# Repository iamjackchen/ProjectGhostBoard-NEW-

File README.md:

# ProjectGhostBoard

Hello thereeee

This is a site for me to document my current ongoing project a low profile wireless mechanical keyboard. Originally started this a few years ago back when I was in middle school (my macbook air had a semi-broken keyboard and I was just getting into the world of mechanical keyboards, AND there was a new set of low profile mechanical switches on the market) 

But who even knows anything about electronics engineering at that age? Took me a few years and attempts to slowly figure stuff out (you can see where I got to in my last attempt here, made when I was in G10: https://github.com/iamjackchen/ProjectGhostboard-OLD-)

<br/>

### About the Project

Enough with the history, moving onto the project itself. The original design goal was to build a low profile (i.e. portable) mechanical keyboard. The portable aspect also prompted me to pursue Bluetooth functionality ~~which might have possibly been the worst decision I have ever made in terms of trying to actually finish this project~~.
Here were my original design blueprints: 

<br/>

<br/>

The design has evolved a little (along with my knowledge of embedded systems and keyboard assembly 😂) but the general principle remains the same. A 75%-ish layout with PCB-mounted low profile switches (PG1350 - I'm using the brown/tactile variant) and white multi-level backlight. No disgusting rgb. Originally when the PG1350 line was released I tried to make this the first true low-profile wireless keyboard on the market but obviously that didn't happen lmao. The layout I eventually settled for is below:

<br/>

<br/>

The current PCB design (in the electronics folder) uses a USB-power gated MOSFET to regulate power delivery from the battery to the main circuit, an MCU-gated MOSFET to control charging (power flow to the battery) and a MCU-gated MOSFET to trigger Bluetooth. The intention of the MCU-gated control charging MOSFET is for the user to be able to disable charging when the keyboard is being plugged in over long periods of time for battery longevity. I'll probably use raw-hid to have some sort of computer-keyboard communication and write a desktop client that can tell the keyboard to disable charging. Maybe in the futre I can use raw-hid and a desktop client for other purposes (macros, backlight settings, and etc)

Some other design considerations and features with regards to electronics:
  - USB Type C
  - Battery charge indicator
  - HID over BLE

The software that makes all of this come together is [QMK](https://github.com/qmk/qmk_firmware). It's a keyboard firmware written in C and I am immensely grateful to its creators. And yes, for all new programmers here, do learn C or C++ before Python and *not* the other way around. You will thank me.

I havent gotten far enough to worry too much about the physical enclosure and keyboard assembly but I will have (hopefully) some CAD files, screenshots, and renders hanging out in this repo soon!! As of now I am aware that the PG1350 requires a thinner (1.2mm) plate and the stabilisers are mounted to the PCB (with plate cutouts needed). 

<br/>
If you've read this far, thank you so much for taking interest, and I hope to bear good news of progress soon. Below is a gallery of certain snippets from this awesome journey. 

----

# Gallery

### Current PCB Progress Renders (Coming soon)
Stay tuned.

<br/>

### Power Delivery Circuit Tester
Small PCB to test out my USB-C power delivery designs. Used an IC originally meant for power bank charging (IP5306 if anyone's interested) along with an FS8205A and a DW01 for battery surge protection. I had a lot of trouble soldering on header pins so I stripped two wires for it. Janky? Yes. But it works 😂

<br/>

<br/>

Here's it in action with a 4000mAh lipo I had lying around from the last attempt at making this keyboard:

<br/>

<br/>

### Proof of Concept
This is a demo of a proof of concept that my parents made me build before they would sponsor any further work of a custom  PCB. On the breadboard I have a Teensy2.0++ (ATUSB1286, the MCU I use in my custom PCB) wired to an Adafruit BLE module via SPI and a 4x4 tester matrix of generic buttons. I built this a while ago but lost the original video so I filmed it again a few days ago. Starring Antoni's new M1X MBP. 

<br/>

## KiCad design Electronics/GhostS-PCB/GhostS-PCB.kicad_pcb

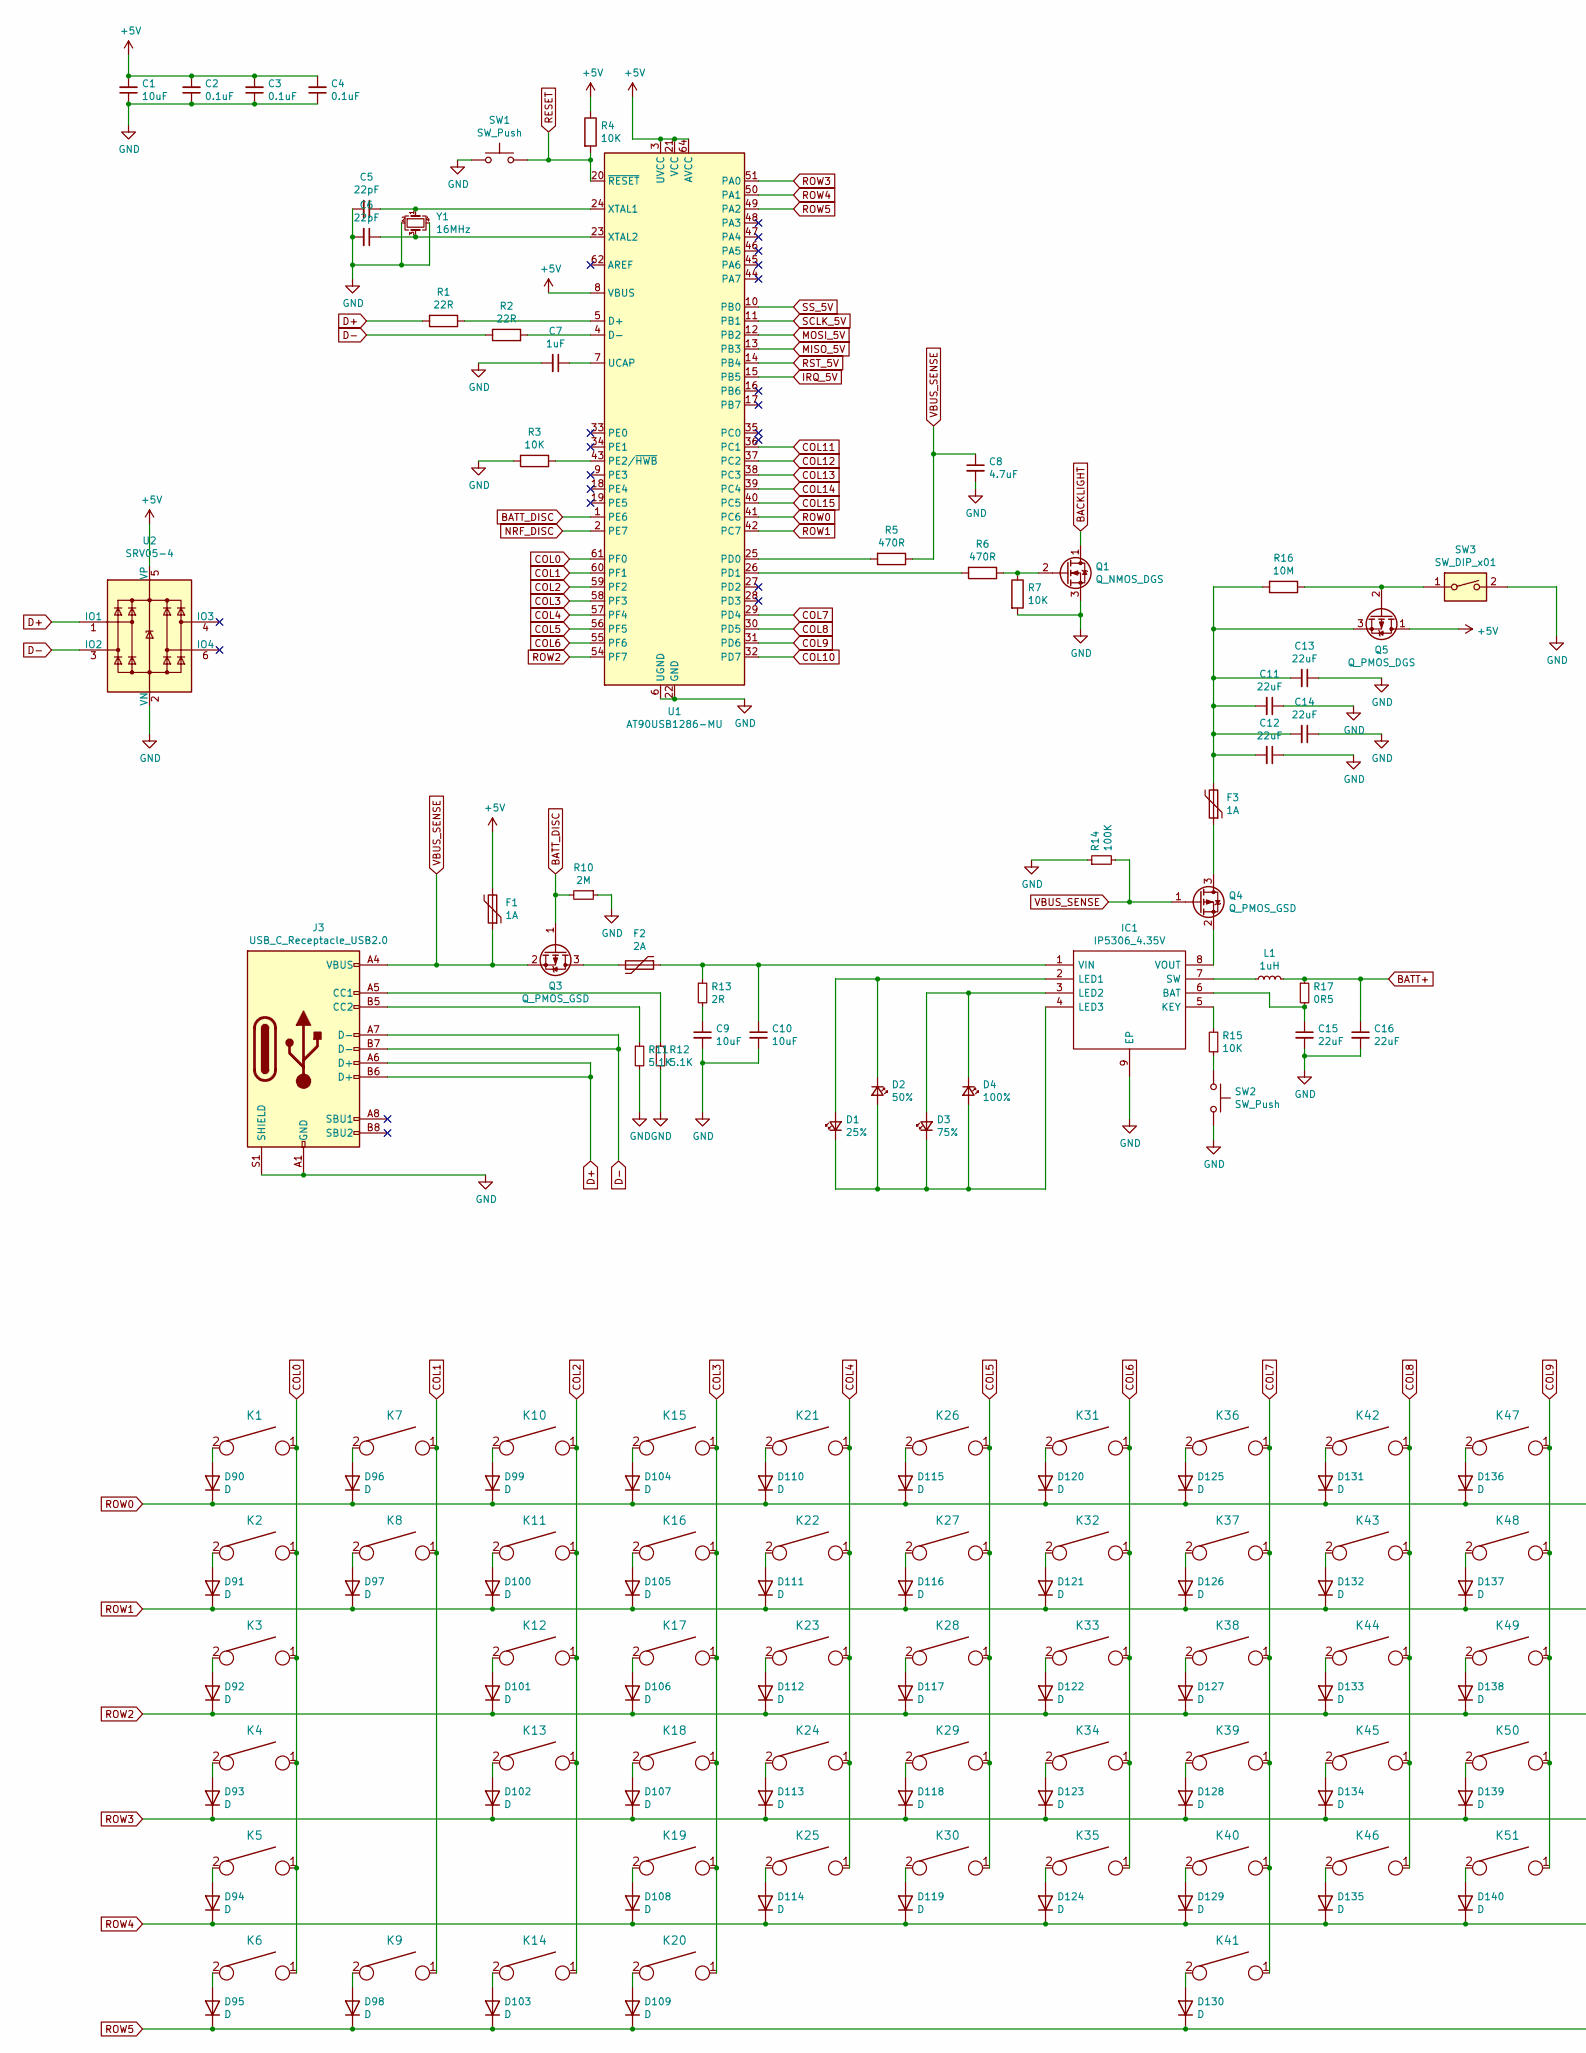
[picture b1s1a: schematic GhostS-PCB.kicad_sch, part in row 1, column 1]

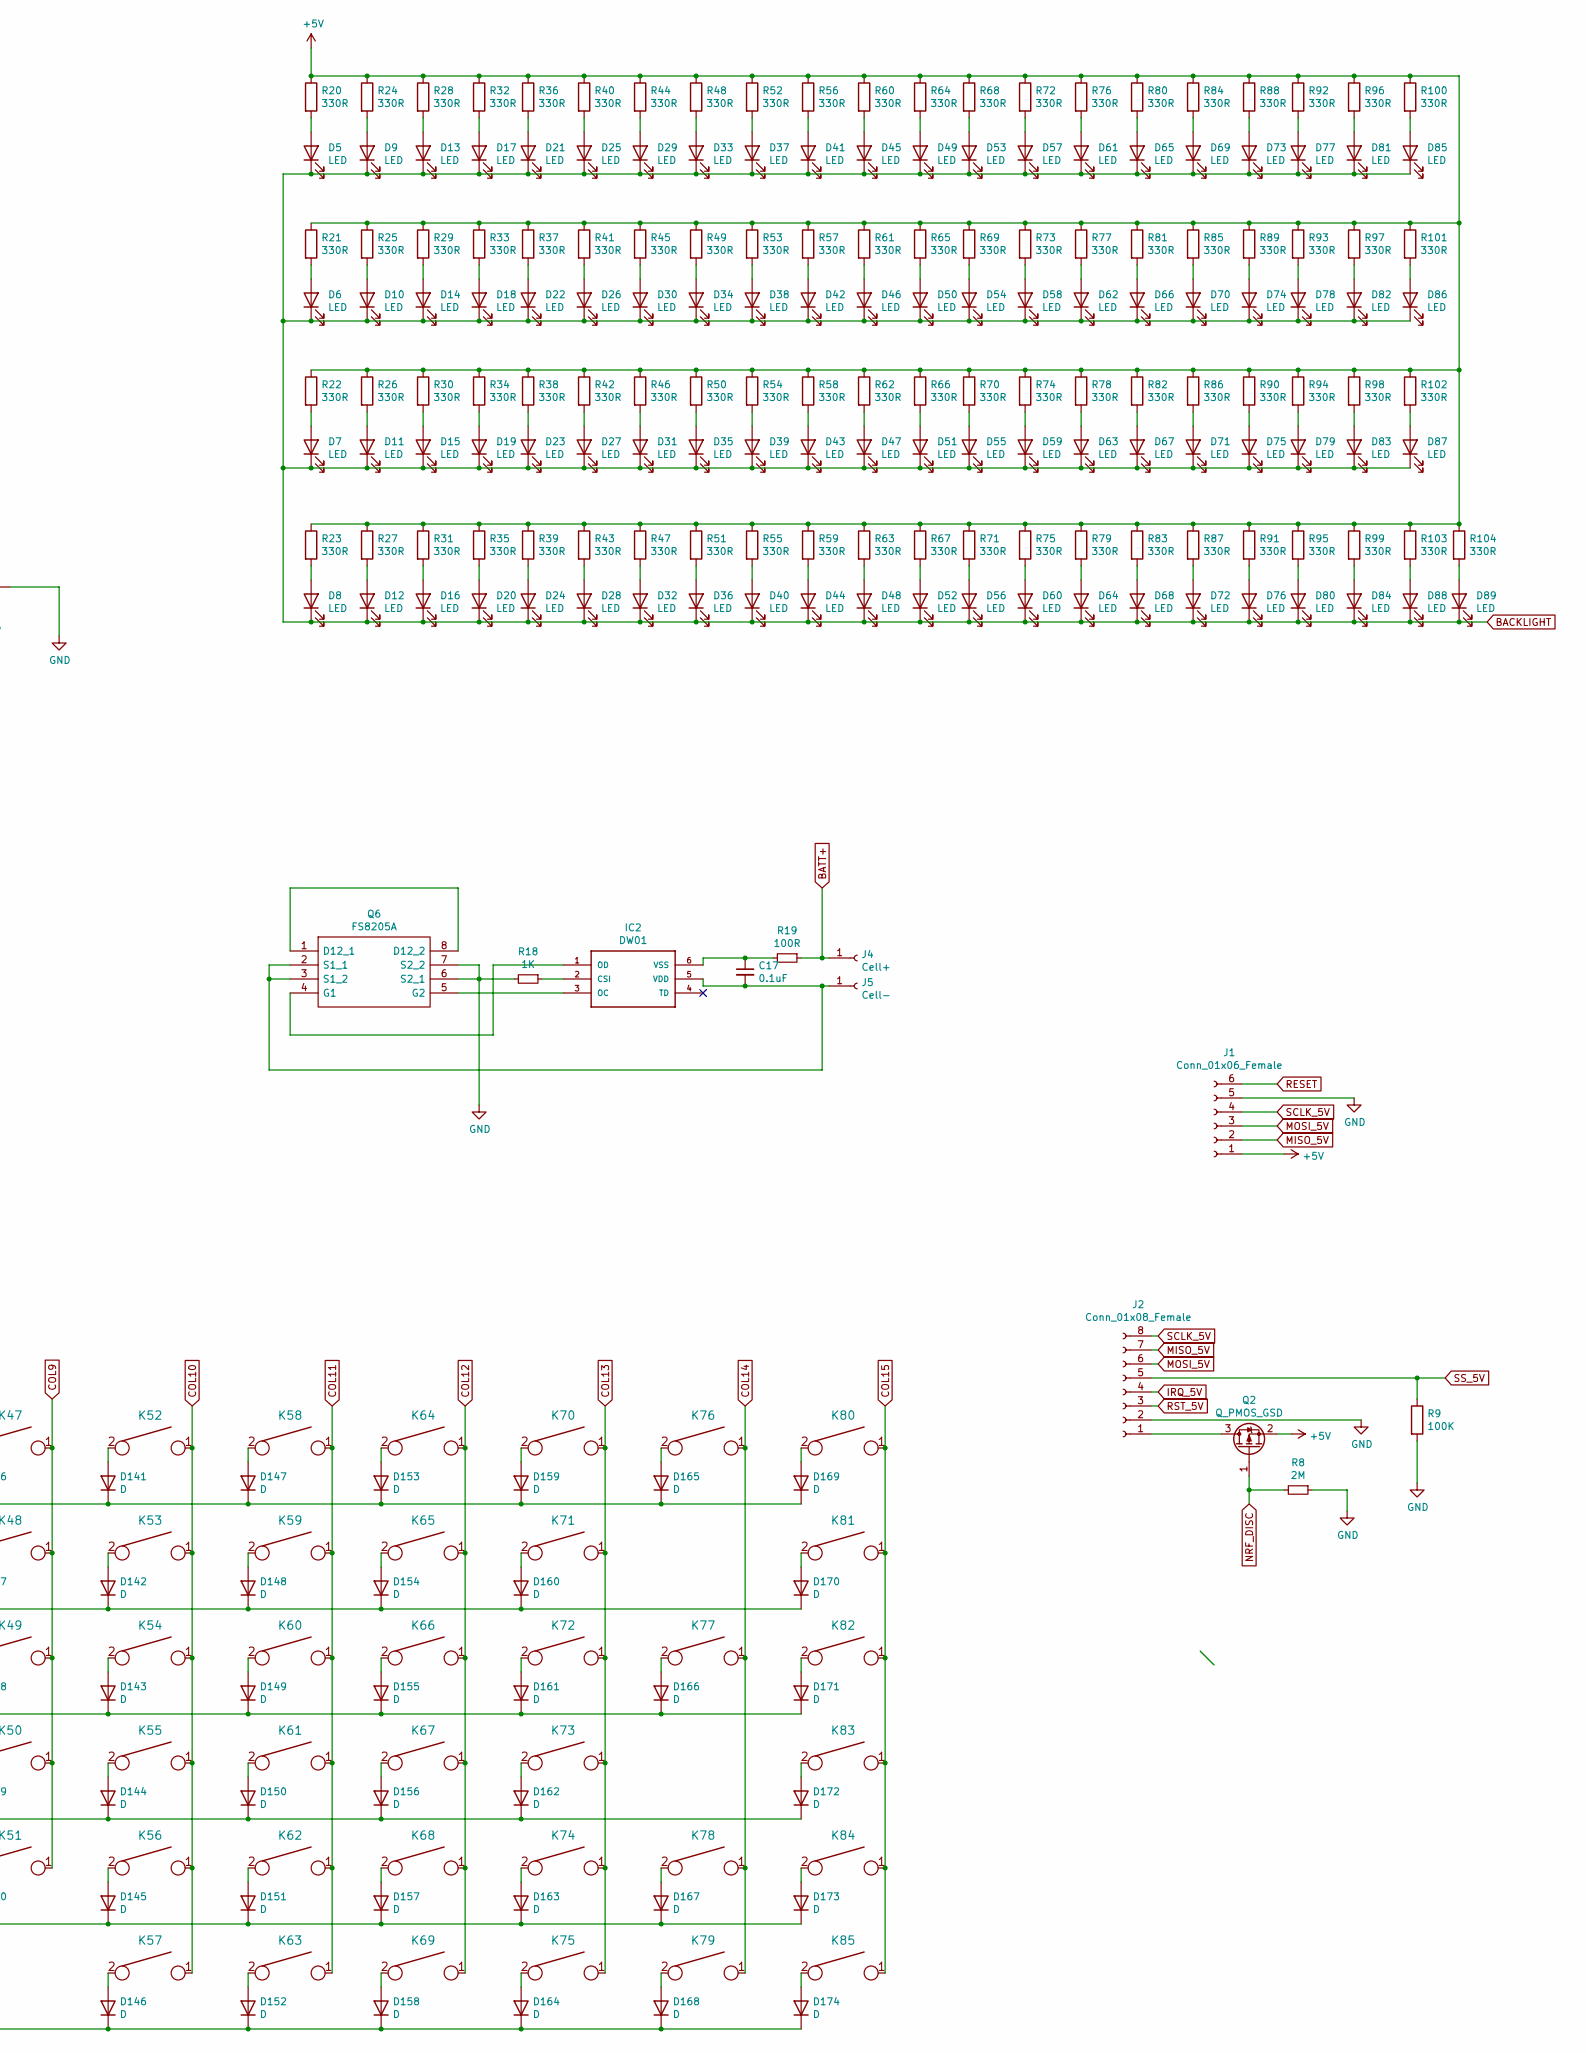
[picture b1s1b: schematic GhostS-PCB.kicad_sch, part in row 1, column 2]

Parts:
C1, C9, C10: 10uF; C_0603_1608Metric
C2, C3, C4, C17: 0.1uF; C_0603_1608Metric
C5, C6: 22pF; C_0603_1608Metric
C7: 1uF; C_0603_1608Metric
C8: 4.7uF; C_0603_1608Metric
C11, C12, C13, C14, C15, C16: 22uF; C_0603_1608Metric
D1: 25%; LED_1206_3216Metric; LCSC C2290
D2: 50%; LED_1206_3216Metric; LCSC C2290
D3: 75%; LED_1206_3216Metric; LCSC C2290
D4: 100%; LED_1206_3216Metric; LCSC C2290
D5, D6, D7, D8, D9, D10, D11, D12, D13, D14, D15, D16, D17, D18, D19, D20, D21, D22, D23, D24, D25, D26, D27, D28, D29, D30, D31, D32, D33, D34, D35, D36, D37, D38, D39, D40, D41, D42, D43, D44, D45, D46, D47, D48, D49, D50, D51, D52, D53, D54, D55, D56, D57, D58, D59, D60, D61, D62, D63, D64, D65, D66, D67, D68, D69, D70, D71, D72, D73, D74, D75, D76, D77, D78, D79, D80, D81, D82, D83, D84, D85, D86, D87, D88, D89: LED; LED_0805_2012Metric
D90, D91, D92, D93, D94, D95, D96, D97, D98, D99, D100, D101, D102, D103, D104, D105, D106, D107, D108, D109, D110, D111, D112, D113, D114, D115, D116, D117, D118, D119, D120, D121, D122, D123, D124, D125, D126, D127, D128, D129, D130, D131, D132, D133, D134, D135, D136, D137, D138, D139, D140, D141, D142, D143, D144, D145, D146, D147, D148, D149, D150, D151, D152, D153, D154, D155, D156, D157, D158, D159, D160, D161, D162, D163, D164, D165, D166, D167, D168, D169, D170, D171, D172, D173, D174: D; D_0603_1608Metric
F1, F3: 1A; Fuse_1206_3216Metric
F2: 2A; Fuse_1206_3216Metric
IC1: IP5306_4.35V; IP5306; LCSC C384572
IC2: DW01; LCSC C14213
J1: Conn_01x06_Female; PinSocket_1x06_P2.54mm_Vertical
J2: Conn_01x08_Female; PinSocket_1x08_P2.54mm_Vertical
J3: USB_C_Receptacle_USB2.0; USB_C_Receptacle_HRO_TYPE-C-31-M-12; LCSC C136423
J4: Cell+; PinSocket_1x01_P2.54mm_Vertical
J5: Cell-; PinSocket_1x01_P2.54mm_Vertical
K1, K2, K3, K6, K7, K8, K9, K10, K11, K12, K13, K14, K15, K16, K17, K18, K19, K20, K21, K22, K23, K24, K25, K26, K27, K28, K29, K30, K31, K32, K33, K34, K35, K36, K37, K38, K39, K40, K42, K43, K44, K45, K46, K47, K48, K49, K50, K51, K52, K53, K54, K55, K56, K57, K58, K59, K60, K61, K62, K63, K64, K65, K66, K67, K68, K69, K70, K72, K74, K75, K76, K77, K78, K79, K80, K81, K82, K83, K84, K85: KEYSW; Kailh-PG1350-1u-NoLED
K4, K5, K71, K73: KEYSW; Kailh-PG1350-2u-NoLED
K41: KEYSW; Kailh-PG1350-5.5u-NoLED
L1: 1uH; L_0805_2012Metric_Pad1.05x1.20mm_HandSolder
Q1: Q_NMOS_DGS; SOT-23
Q2, Q3, Q4: Q_PMOS_GSD; SOT-23
Q5: Q_PMOS_DGS; SOT-23
Q6: FS8205A; LCSC C16052
R1, R2: 22R; R_0603_1608Metric
R3, R4, R7, R15: 10K; R_0603_1608Metric
R5, R6: 470R; R_0603_1608Metric
R8, R10: 2M; R_0603_1608Metric
R9, R14: 100K; R_0603_1608Metric
R11, R12: 5.1K; R_0603_1608Metric
R13: 2R; R_0603_1608Metric
R16: 10M; R_0603_1608Metric
R17: 0R5; R_0603_1608Metric
R18: 1K; R_0603_1608Metric
R19: 100R; R_0603_1608Metric
R20, R21, R22, R23, R24, R25, R26, R27, R28, R29, R30, R31, R32, R33, R34, R35, R36, R37, R38, R39, R40, R41, R42, R43, R44, R45, R46, R47, R48, R49, R50, R51, R52, R53, R54, R55, R56, R57, R58, R59, R60, R61, R62, R63, R64, R65, R66, R67, R68, R69, R70, R71, R72, R73, R74, R75, R76, R77, R78, R79, R80, R81, R82, R83, R84, R85, R86, R87, R88, R89, R90, R91, R92, R93, R94, R95, R96, R97, R98, R99, R100, R101, R102, R103, R104: 330R; R_0603_1608Metric
SW1: SW_Push; SW_SPST_SKQG_WithStem
SW2: SW_Push; TS-1186D
SW3: SW_DIP_x01; SW-TH_SK-3245D-02-L4.00
U1: AT90USB1286-MU; QFN-64-1EP_9x9mm_P0.5mm_EP7.5x7.5mm
U2: SRV05-4; SOT-23-6
Y1: 16MHz; Crystal_SMD_3225-4pin_3.2x2.5mm

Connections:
+5V: C1.2, C2.2, C3.2, C4.2, F1.2, J1.1, Q2.2 (S), Q5.1 (D), R4.1, R20.1, R21.1, R22.1, R23.1, R24.1, R25.1, R26.1, R27.1, R28.1, R29.1, R30.1, R31.1, R32.1, R33.1, R34.1, R35.1, R36.1, R37.1, R38.1, R39.1, R40.1, R41.1, R42.1, R43.1, R44.1, R45.1, R46.1, R47.1, R48.1, R49.1, R50.1, R51.1, R52.1, R53.1, R54.1, R55.1, R56.1, R57.1, R58.1, R59.1, R60.1, R61.1, R62.1, R63.1, R64.1, R65.1, R66.1, R67.1, R68.1, R69.1, R70.1, R71.1, R72.1, R73.1, R74.1, R75.1, R76.1, R77.1, R78.1, R79.1, R80.1, R81.1, R82.1, R83.1, R84.1, R85.1, R86.1, R87.1, R88.1, R89.1, R90.1, R91.1, R92.1, R93.1, R94.1, R95.1, R96.1, R97.1, R98.1, R99.1, R100.1, R101.1, R102.1, R103.1, R104.1, U1.3 (UVCC), U1.8 (VBUS), U1.21 (VCC), U1.52 (VCC), U1.64 (AVCC), U2.5 (VP); also elsewhere on the board
BACKLIGHT: D5.1 (K), D6.1 (K), D7.1 (K), D8.1 (K), D9.1 (K), D10.1 (K), D11.1 (K), D12.1 (K), D13.1 (K), D14.1 (K), D15.1 (K), D16.1 (K), D17.1 (K), D18.1 (K), D19.1 (K), D20.1 (K), D21.1 (K), D22.1 (K), D23.1 (K), D24.1 (K), D25.1 (K), D26.1 (K), D27.1 (K), D28.1 (K), D29.1 (K), D30.1 (K), D31.1 (K), D32.1 (K), D33.1 (K), D34.1 (K), D35.1 (K), D36.1 (K), D37.1 (K), D38.1 (K), D39.1 (K), D40.1 (K), D41.1 (K), D42.1 (K), D43.1 (K), D44.1 (K), D45.1 (K), D46.1 (K), D47.1 (K), D48.1 (K), D49.1 (K), D50.1 (K), D51.1 (K), D52.1 (K), D53.1 (K), D54.1 (K), D55.1 (K), D56.1 (K), D57.1 (K), D58.1 (K), D59.1 (K), D60.1 (K), D61.1 (K), D62.1 (K), D63.1 (K), D64.1 (K), D65.1 (K), D66.1 (K), D67.1 (K), D68.1 (K), D69.1 (K), D70.1 (K), D71.1 (K), D72.1 (K), D73.1 (K), D74.1 (K), D75.1 (K), D76.1 (K), D77.1 (K), D78.1 (K), D79.1 (K), D80.1 (K), D81.1 (K), D82.1 (K), D83.1 (K), D84.1 (K), D85.1 (K), D86.1 (K), D87.1 (K), D88.1 (K), D89.1 (K), Q1.1 (D)
BATT+: C16.1, J4.1, L1.2, R17.1, R19.1
BATT_DISC: Q3.1 (G), R10.2, U1.1 (PE6)
COL0: K1.1, K2.1, K3.1, K4.1, K5.1, K6.1, U1.61 (PF0)
COL1: K7.1, K8.1, K9.1, U1.60 (PF1)
COL2: K10.1, K11.1, K12.1, K13.1, K14.1, U1.59 (PF2)
COL3: K15.1, K16.1, K17.1, K18.1, K19.1, K20.1, U1.58 (PF3)
COL4: K21.1, K22.1, K23.1, K24.1, K25.1, U1.57 (PF4)
COL5: K26.1, K27.1, K28.1, K29.1, K30.1, U1.56 (PF5)
COL6: K31.1, K32.1, K33.1, K34.1, K35.1, U1.55 (PF6)
COL7: K36.1, K37.1, K38.1, K39.1, K40.1, K41.1, U1.29 (PD4)
COL8: K42.1, K43.1, K44.1, K45.1, K46.1, U1.30 (PD5)
COL9: K47.1, K48.1, K49.1, K50.1, K51.1, U1.31 (PD6)
COL10: K52.1, K53.1, K54.1, K55.1, K56.1, K57.1, U1.32 (PD7)
COL11: K58.1, K59.1, K60.1, K61.1, K62.1, K63.1, U1.36 (PC1)
COL12: K64.1, K65.1, K66.1, K67.1, K68.1, K69.1, U1.37 (PC2)
COL13: K70.1, K71.1, K72.1, K73.1, K74.1, K75.1, U1.38 (PC3)
COL14: K76.1, K77.1, K78.1, K79.1, U1.39 (PC4)
COL15: K80.1, K81.1, K82.1, K83.1, K84.1, K85.1, U1.40 (PC5)
D+: J3.A6 (D+), J3.B6 (D+), R1.2, U2.1 (IO1)
D-: J3.A7 (D-), J3.B7 (D-), R2.1, U2.3 (IO2)
GND: C1.1, C2.1, C3.1, C4.1, C5.2, C6.2, C7.2, C8.2, C9.2, C10.2, C11.1, C12.1, C13.1, C14.1, C15.2, C16.2, IC1.9 (EP), J1.5, J2.2, J3.A1 (GND), J3.A12 (GND), J3.B1 (GND), J3.B12 (GND), J3.S1 (SHIELD), Q1.3 (S), Q6.6 (S2_1), Q6.7 (S2_2), R3.2, R7.2, R8.1, R9.2, R10.1, R11.2, R12.2, R14.1, R18.2, SW1.1, SW2.2, SW3.2, U1.6 (UGND), U1.22 (GND), U1.53 (GND), U1.63 (GND), U1.65 (GND), U2.2 (VN), Y1.2, Y1.4
IRQ_5V: J2.4, U1.15 (PB5)
MISO_5V: J1.2, J2.7, U1.13 (PB3)
MOSI_5V: J1.3, J2.6, U1.12 (PB2)
NRF_DISC: Q2.1 (G), R8.2, U1.2 (PE7)
unnamed: C5.1, U1.24 (XTAL1), Y1.1
unnamed: C6.1, U1.23 (XTAL2), Y1.3
unnamed: C7.1, U1.7 (UCAP)
unnamed: C9.1, R13.2
unnamed: C10.1, F2.1, IC1.1 (VIN), R13.1
unnamed: C11.2, C12.2, C13.2, C14.2, F3.2, Q5.3 (S), R16.2
unnamed: C15.1, IC1.6 (BAT), R17.2
unnamed: C17.1, IC2.6 (VSS), R19.2
unnamed: C17.2, IC2.5 (VDD), J5.1, Q6.2 (S1_1), Q6.3 (S1_2)
unnamed: D1.1 (K), D2.2 (A), D3.1 (K), D4.2 (A), IC1.4 (LED3)
unnamed: D1.2 (A), D2.1 (K), IC1.2 (LED1)
unnamed: D3.2 (A), D4.1 (K), IC1.3 (LED2)
unnamed: D5.2 (A), R20.2
unnamed: D6.2 (A), R21.2
unnamed: D7.2 (A), R22.2
unnamed: D8.2 (A), R23.2
unnamed: D9.2 (A), R24.2
unnamed: D10.2 (A), R25.2
unnamed: D11.2 (A), R26.2
unnamed: D12.2 (A), R27.2
unnamed: D13.2 (A), R28.2
unnamed: D14.2 (A), R29.2
unnamed: D15.2 (A), R30.2
unnamed: D16.2 (A), R31.2
unnamed: D17.2 (A), R32.2
unnamed: D18.2 (A), R33.2
unnamed: D19.2 (A), R34.2
unnamed: D20.2 (A), R35.2
unnamed: D21.2 (A), R36.2
unnamed: D22.2 (A), R37.2
unnamed: D23.2 (A), R38.2
unnamed: D24.2 (A), R39.2
unnamed: D25.2 (A), R40.2
unnamed: D26.2 (A), R41.2
unnamed: D27.2 (A), R42.2
unnamed: D28.2 (A), R43.2
unnamed: D29.2 (A), R44.2
unnamed: D30.2 (A), R45.2
unnamed: D31.2 (A), R46.2
unnamed: D32.2 (A), R47.2
unnamed: D33.2 (A), R48.2
unnamed: D34.2 (A), R49.2
unnamed: D35.2 (A), R50.2
unnamed: D36.2 (A), R51.2
unnamed: D37.2 (A), R52.2
unnamed: D38.2 (A), R53.2
unnamed: D39.2 (A), R54.2
unnamed: D40.2 (A), R55.2
unnamed: D41.2 (A), R56.2
unnamed: D42.2 (A), R57.2
unnamed: D43.2 (A), R58.2
unnamed: D44.2 (A), R59.2
unnamed: D45.2 (A), R60.2
unnamed: D46.2 (A), R61.2
unnamed: D47.2 (A), R62.2
unnamed: D48.2 (A), R63.2
unnamed: D49.2 (A), R64.2
unnamed: D50.2 (A), R65.2
unnamed: D51.2 (A), R66.2
unnamed: D52.2 (A), R67.2
unnamed: D53.2 (A), R68.2
unnamed: D54.2 (A), R69.2
unnamed: D55.2 (A), R70.2
unnamed: D56.2 (A), R71.2
unnamed: D57.2 (A), R72.2
unnamed: D58.2 (A), R73.2
unnamed: D59.2 (A), R74.2
unnamed: D60.2 (A), R75.2
unnamed: D61.2 (A), R76.2
unnamed: D62.2 (A), R77.2
unnamed: D63.2 (A), R78.2
unnamed: D64.2 (A), R79.2
unnamed: D65.2 (A), R80.2
unnamed: D66.2 (A), R81.2
unnamed: D67.2 (A), R82.2
unnamed: D68.2 (A), R83.2
unnamed: D69.2 (A), R84.2
unnamed: D70.2 (A), R85.2
unnamed: D71.2 (A), R86.2
unnamed: D72.2 (A), R87.2
unnamed: D73.2 (A), R88.2
unnamed: D74.2 (A), R89.2
unnamed: D75.2 (A), R90.2
unnamed: D76.2 (A), R91.2
unnamed: D77.2 (A), R92.2
unnamed: D78.2 (A), R93.2
unnamed: D79.2 (A), R94.2
unnamed: D80.2 (A), R95.2
unnamed: D81.2 (A), R96.2
unnamed: D82.2 (A), R97.2
unnamed: D83.2 (A), R98.2
unnamed: D84.2 (A), R99.2
unnamed: D85.2 (A), R100.2
unnamed: D86.2 (A), R101.2
unnamed: D87.2 (A), R102.2
unnamed: D88.2 (A), R103.2
unnamed: D89.2 (A), R104.2
unnamed: D90.2 (A), K1.2
unnamed: D91.2 (A), K2.2
unnamed: D92.2 (A), K3.2
unnamed: D93.2 (A), K4.2
unnamed: D94.2 (A), K5.2
unnamed: D95.2 (A), K6.2
unnamed: D96.2 (A), K7.2
unnamed: D97.2 (A), K8.2
unnamed: D98.2 (A), K9.2
unnamed: D99.2 (A), K10.2
unnamed: D100.2 (A), K11.2
unnamed: D101.2 (A), K12.2
unnamed: D102.2 (A), K13.2
unnamed: D103.2 (A), K14.2
unnamed: D104.2 (A), K15.2
unnamed: D105.2 (A), K16.2
unnamed: D106.2 (A), K17.2
unnamed: D107.2 (A), K18.2
unnamed: D108.2 (A), K19.2
unnamed: D109.2 (A), K20.2
unnamed: D110.2 (A), K21.2
unnamed: D111.2 (A), K22.2
unnamed: D112.2 (A), K23.2
unnamed: D113.2 (A), K24.2
unnamed: D114.2 (A), K25.2
unnamed: D115.2 (A), K26.2
unnamed: D116.2 (A), K27.2
unnamed: D117.2 (A), K28.2
unnamed: D118.2 (A), K29.2
unnamed: D119.2 (A), K30.2
unnamed: D120.2 (A), K31.2
unnamed: D121.2 (A), K32.2
unnamed: D122.2 (A), K33.2
unnamed: D123.2 (A), K34.2
unnamed: D124.2 (A), K35.2
unnamed: D125.2 (A), K36.2
unnamed: D126.2 (A), K37.2
unnamed: D127.2 (A), K38.2
unnamed: D128.2 (A), K39.2
unnamed: D129.2 (A), K40.2
unnamed: D130.2 (A), K41.2
unnamed: D131.2 (A), K42.2
unnamed: D132.2 (A), K43.2
unnamed: D133.2 (A), K44.2
unnamed: D134.2 (A), K45.2
unnamed: D135.2 (A), K46.2
unnamed: D136.2 (A), K47.2
unnamed: D137.2 (A), K48.2
unnamed: D138.2 (A), K49.2
unnamed: D139.2 (A), K50.2
unnamed: D140.2 (A), K51.2
unnamed: D141.2 (A), K52.2
unnamed: D142.2 (A), K53.2
unnamed: D143.2 (A), K54.2
unnamed: D144.2 (A), K55.2
unnamed: D145.2 (A), K56.2
unnamed: D146.2 (A), K57.2
unnamed: D147.2 (A), K58.2
unnamed: D148.2 (A), K59.2
unnamed: D149.2 (A), K60.2
unnamed: D150.2 (A), K61.2
unnamed: D151.2 (A), K62.2
unnamed: D152.2 (A), K63.2
unnamed: D153.2 (A), K64.2
unnamed: D154.2 (A), K65.2
unnamed: D155.2 (A), K66.2
unnamed: D156.2 (A), K67.2
unnamed: D157.2 (A), K68.2
unnamed: D158.2 (A), K69.2
unnamed: D159.2 (A), K70.2
unnamed: D160.2 (A), K71.2
unnamed: D161.2 (A), K72.2
unnamed: D162.2 (A), K73.2
unnamed: D163.2 (A), K74.2
unnamed: D164.2 (A), K75.2
unnamed: D165.2 (A), K76.2
unnamed: D166.2 (A), K77.2
unnamed: D167.2 (A), K78.2
unnamed: D168.2 (A), K79.2
unnamed: D169.2 (A), K80.2
unnamed: D170.2 (A), K81.2
unnamed: D171.2 (A), K82.2
unnamed: D172.2 (A), K83.2
unnamed: D173.2 (A), K84.2
unnamed: D174.2 (A), K85.2
unnamed: F2.2, Q3.3 (D)
unnamed: F3.1, Q4.3 (D)
unnamed: IC1.5 (KEY), R15.2
unnamed: IC1.7 (SW), L1.1
unnamed: IC1.8 (VOUT), Q4.2 (S)
unnamed: IC2.1 (OD), Q6.4 (G1)
unnamed: IC2.2 (CSI), R18.1
unnamed: IC2.3 (OC), Q6.5 (G2)
unnamed: J2.1, Q2.3 (D)
unnamed: J3.A5 (CC1), R12.1
unnamed: J3.B5 (CC2), R11.1
unnamed: Q1.2 (G), R6.1, R7.1
unnamed: Q5.2 (G), R16.1, SW3.1
unnamed: Q6.1 (D12_1), Q6.8 (D12_2)
unnamed: R1.1, U1.5 (D+)
unnamed: R2.2, U1.4 (D-)
unnamed: R3.1, U1.43 (PE2/~HWB)
unnamed: R5.2, U1.25 (PD0)
unnamed: R6.2, U1.26 (PD1)
unnamed: R15.1, SW2.1
RESET: J1.6, R4.2, SW1.2, U1.20 (~RESET)
ROW0: D90.1 (K), D96.1 (K), D99.1 (K), D104.1 (K), D110.1 (K), D115.1 (K), D120.1 (K), D125.1 (K), D131.1 (K), D136.1 (K), D141.1 (K), D147.1 (K), D153.1 (K), D159.1 (K), D165.1 (K), D169.1 (K), U1.41 (PC6)
ROW1: D91.1 (K), D97.1 (K), D100.1 (K), D105.1 (K), D111.1 (K), D116.1 (K), D121.1 (K), D126.1 (K), D132.1 (K), D137.1 (K), D142.1 (K), D148.1 (K), D154.1 (K), D160.1 (K), D170.1 (K), U1.42 (PC7)
ROW2: D92.1 (K), D101.1 (K), D106.1 (K), D112.1 (K), D117.1 (K), D122.1 (K), D127.1 (K), D133.1 (K), D138.1 (K), D143.1 (K), D149.1 (K), D155.1 (K), D161.1 (K), D166.1 (K), D171.1 (K), U1.54 (PF7)
ROW3: D93.1 (K), D102.1 (K), D107.1 (K), D113.1 (K), D118.1 (K), D123.1 (K), D128.1 (K), D134.1 (K), D139.1 (K), D144.1 (K), D150.1 (K), D156.1 (K), D162.1 (K), D172.1 (K), U1.51 (PA0)
ROW4: D94.1 (K), D108.1 (K), D114.1 (K), D119.1 (K), D124.1 (K), D129.1 (K), D135.1 (K), D140.1 (K), D145.1 (K), D151.1 (K), D157.1 (K), D163.1 (K), D167.1 (K), D173.1 (K), U1.50 (PA1)
ROW5: D95.1 (K), D98.1 (K), D103.1 (K), D109.1 (K), D130.1 (K), D146.1 (K), D152.1 (K), D158.1 (K), D164.1 (K), D168.1 (K), D174.1 (K), U1.49 (PA2)
RST_5V: J2.3, U1.14 (PB4)
SCLK_5V: J1.4, J2.8, U1.11 (PB1)
SS_5V: J2.5, R9.1, U1.10 (PB0)
VBUS_SENSE: C8.1, F1.1, J3.A4 (VBUS), J3.A9 (VBUS), J3.B4 (VBUS), J3.B9 (VBUS), Q3.2 (S), Q4.1 (G), R5.1, R14.2

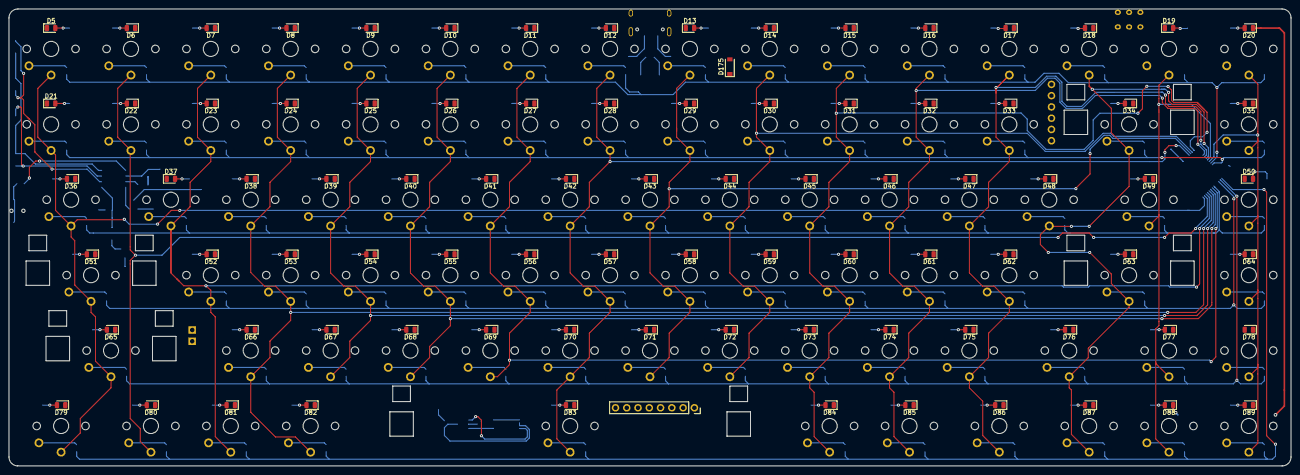
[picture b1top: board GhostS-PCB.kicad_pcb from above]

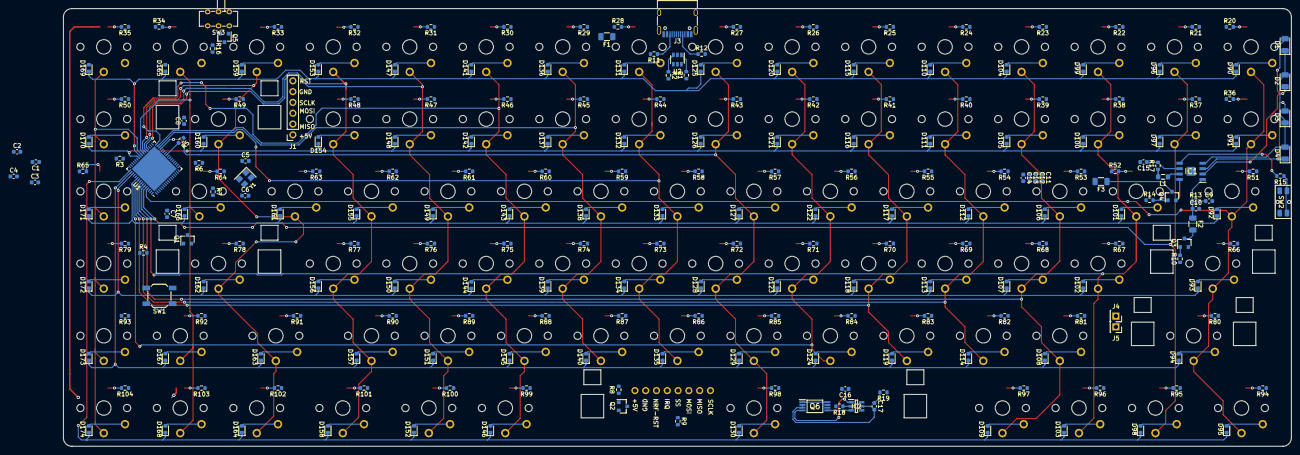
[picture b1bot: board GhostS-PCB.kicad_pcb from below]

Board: 2 copper layers, 289.0 x 103.0 mm, 404 parts (232 on the bottom side), 240 nets.

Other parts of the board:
D175: D_Schottky; D_SOD-123

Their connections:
+5V: D175.1; also elsewhere on the board

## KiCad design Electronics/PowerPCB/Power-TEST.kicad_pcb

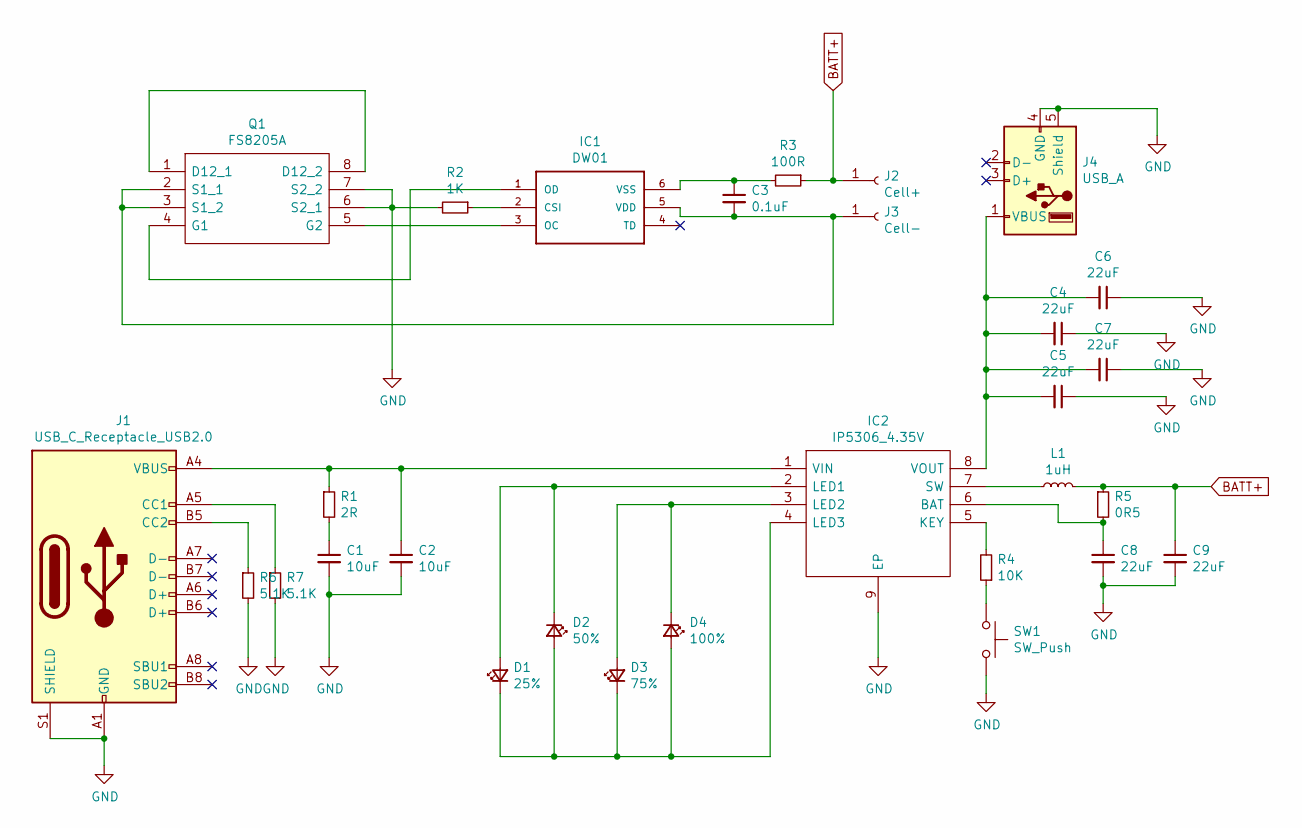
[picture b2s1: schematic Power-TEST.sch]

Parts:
C1, C2: 10uF; C_0805_2012Metric_Pad1.18x1.45mm_HandSolder
C3: 0.1uF; C_0603_1608Metric_Pad1.08x0.95mm_HandSolder
C4, C5, C6, C7, C8, C9: 22uF; C_0805_2012Metric_Pad1.18x1.45mm_HandSolder
D1: 25%; LED_0805_2012Metric_Pad1.15x1.40mm_HandSolder; LCSC C2290
D2: 50%; LED_0805_2012Metric_Pad1.15x1.40mm_HandSolder; LCSC C2290
D3: 75%; LED_0805_2012Metric_Pad1.15x1.40mm_HandSolder; LCSC C2290
D4: 100%; LED_0805_2012Metric_Pad1.15x1.40mm_HandSolder; LCSC C2290
IC1: DW01; LCSC C14213
IC2: IP5306_4.35V; IP5306; LCSC C384572
J1: USB_C_Receptacle_USB2.0; USB_C_Receptacle_HRO_TYPE-C-31-M-12; LCSC C136423
J2: Cell+; PinSocket_1x01_P2.54mm_Vertical
J3: Cell-; PinSocket_1x01_P2.54mm_Vertical
J4: USB_A; USB_A_Stewart_SS-52100-001_Horizontal; LCSC C2346
L1: 1uH; L_0805_2012Metric_Pad1.05x1.20mm_HandSolder
Q1: FS8205A; LCSC C16052
R1: 2R; R_0805_2012Metric_Pad1.20x1.40mm_HandSolder
R2: 1K; R_0805_2012Metric_Pad1.20x1.40mm_HandSolder
R3: 100R; R_0805_2012Metric_Pad1.20x1.40mm_HandSolder
R4: 10K; R_0805_2012Metric_Pad1.20x1.40mm_HandSolder
R5: 0R5; R_0805_2012Metric_Pad1.20x1.40mm_HandSolder
R6, R7: 5.1K; R_0805_2012Metric_Pad1.20x1.40mm_HandSolder
SW1: SW_Push; SW_PUSH_6mm_H4.3mm

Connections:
BATT+: C9.1, J2.1, L1.2, R3.1, R5.1
GND: C1.2, C2.2, C4.1, C5.1, C6.1, C7.1, C8.2, C9.2, IC2.9 (EP), J1.A1 (GND), J1.A12 (GND), J1.B1 (GND), J1.B12 (GND), J1.S1 (SHIELD), J4.4 (GND), J4.5 (Shield), Q1.6 (S2_1), Q1.7 (S2_2), R2.2, R6.2, R7.2, SW1.2
unnamed: C1.1, R1.2
unnamed: C2.1, IC2.1 (VIN), J1.A4 (VBUS), J1.A9 (VBUS), J1.B4 (VBUS), J1.B9 (VBUS), R1.1
unnamed: C3.1, IC1.6 (VSS), R3.2
unnamed: C3.2, IC1.5 (VDD), J3.1, Q1.2 (S1_1), Q1.3 (S1_2)
unnamed: C4.2, C5.2, C6.2, C7.2, IC2.8 (VOUT), J4.1 (VBUS)
unnamed: C8.1, IC2.6 (BAT), R5.2
unnamed: D1.1 (K), D2.2 (A), D3.1 (K), D4.2 (A), IC2.4 (LED3)
unnamed: D1.2 (A), D2.1 (K), IC2.2 (LED1)
unnamed: D3.2 (A), D4.1 (K), IC2.3 (LED2)
unnamed: IC1.1 (OD), Q1.4 (G1)
unnamed: IC1.2 (CSI), R2.1
unnamed: IC1.3 (OC), Q1.5 (G2)
unnamed: IC2.5 (KEY), R4.2
unnamed: IC2.7 (SW), L1.1
unnamed: J1.A5 (CC1), R7.1
unnamed: J1.B5 (CC2), R6.1
unnamed: Q1.1 (D12_1), Q1.8 (D12_2)
unnamed: R4.1, SW1.1

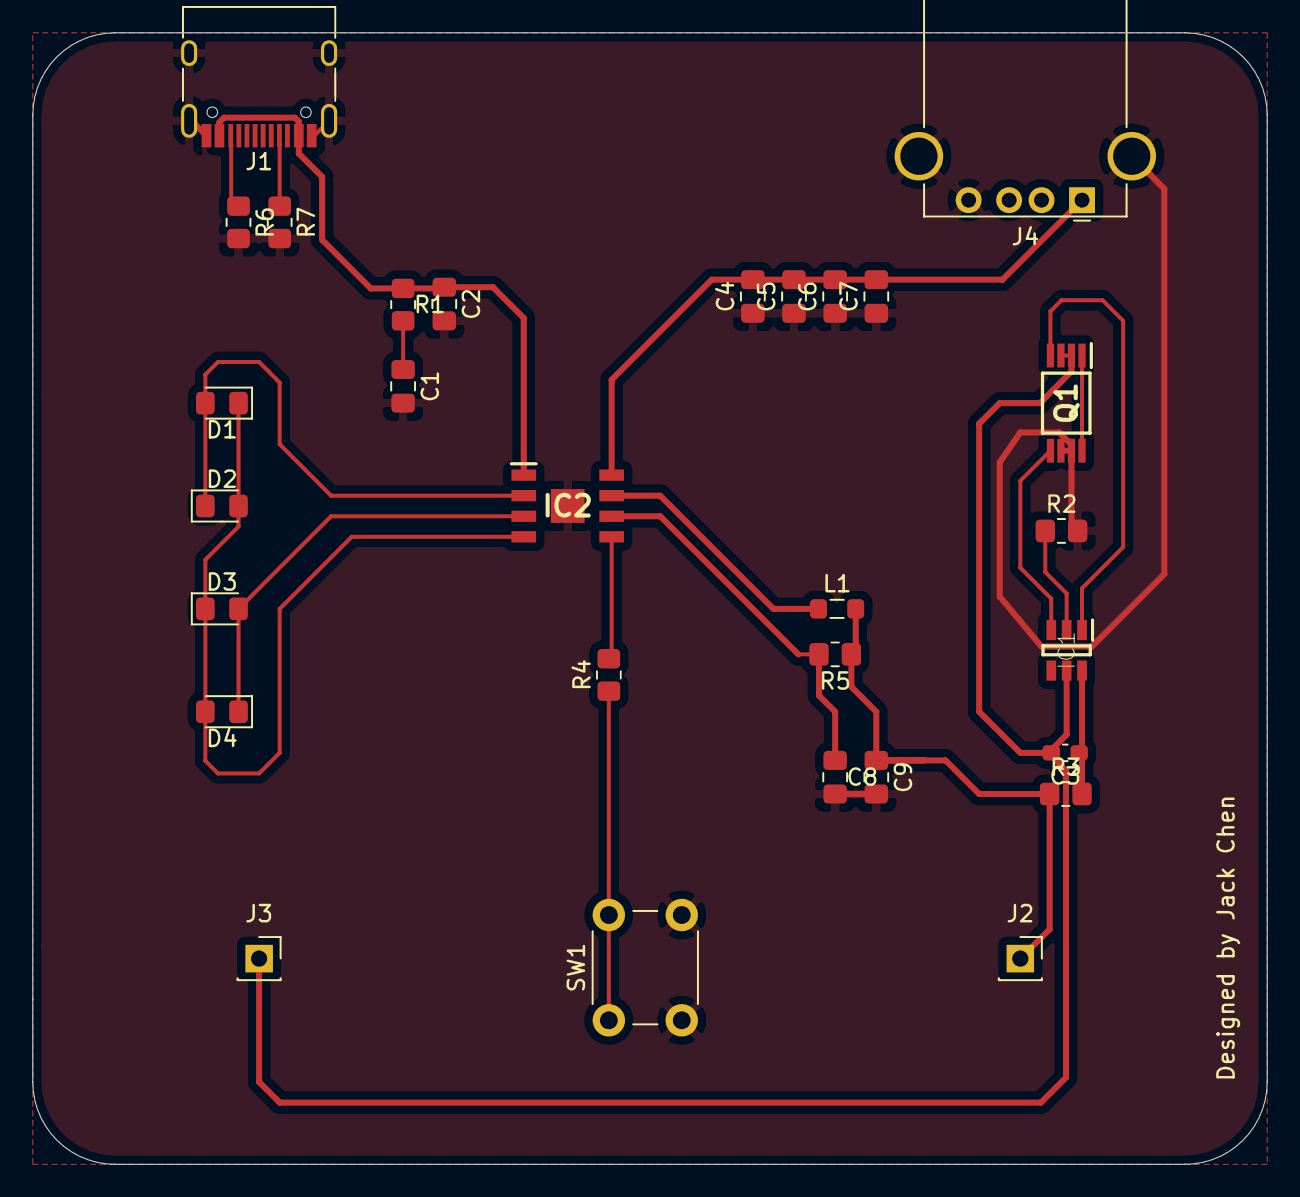
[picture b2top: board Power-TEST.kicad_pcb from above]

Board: 2 copper layers, 76.2 x 69.8 mm, 29 parts (0 on the bottom side), 20 nets.

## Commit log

2022-01-10 nice
2022-01-11 added photoes
2022-01-11 More photos
2022-01-12 embed video
2022-01-12 embed video 2
2022-01-12 photos
